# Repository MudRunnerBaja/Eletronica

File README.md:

# Eletronica
Repositório a ser usado apenas pelos membros de eletrônica da equipe baja do Cefet-RJ <br />
Por favor, ao fazer uma alteração no código, indicar o que foi alterado e colocar no READ.ME <br />

## Microcontroladores

- __Pic__:É um microcontrolador de arquitetura Harvard fabricado pela Microchip technology, ele tem a capacidade de processar dados de 8 bits, 16 bits e na versão mais atual, ele é capaz de processar dados de 32 bits. Ele possui uma alta velocidade de processamento devido a sua arquitetura Harvard, além disso, as famílias do MCU Pic  tem núcleos de processamento de 12bits, 14bits e 16bits, e trabalham em velocidade 0kHZ 48MHZ e velocidades de 16MIPS em alguns modelos.<br />   

- __Arduino__:Arduino é uma plataforma de prototipagem eletrônica de hardware livre e de placa única, projetada com um microcontrolador Atmel AVR com suporte de entrada/saída embutido, uma linguagem de programação padrão, a qual tem origem em Wiring, e é essencialmente C/C++.  Normalmente é utilizado em projetos mais simples e que não necessitam de conhecimento muito avançado sobre o firmware do microcontrolador (projetos caseiros).<br /> 

- __Esp32__:É um microcontrolador, que emprega um microprocessador de arquitetura Tensilica Xtensa LX6 de 32 bits com variações dual e single core e uma memória SRAM de 512Kb. Possui um clock máximo de 240 MHz. Ele também conta com wifi e bluetooth integrado.<br /> 

- __STM Arm__:STM32 é uma família de microcontroladores de 32 bits produzidos pela STMicroelectronics. Os chips STM32 são agrupados em séries relacionadas que são baseados em torno do mesmo núcleo do processador ARM de 32 bits, como o Cortex-M7, Cortex-M4F, Cortex-M3, Cortex-M0 +, ou Cortex-M0.<br /> 

- __RP2040__: O RP2040 é um microcontrolador de baixo custo e boa performance, criado pela Raspberry Pi. Trata-se de um processador Dual-Core ARM Cortex M0+, rodando em até 133MHz. Possui 264kB de memória SRAM e 2MB de memória Flash integrada na placa e pode ser programado em MicroPhython ou C/C++. O RP2040 possui 26 GPIOs multifunção, com 2x SPI, 2x I2C, 2x UART, 3x ADC de 12-bits e 16 canais PWM. Ela inclui um sensor de temperatura e bibliotecas para tratar ponto flutuante.<br />

### Microcontrolador escolhido pela equipe

O microcontrolador selecionado pela equipe é o RP2040, vendo sua alta performance, baixo custo e a possibilidade de ser programado pela IDE do arduino. A possibilidade de ser programado pela IDE do Arduino cria uma facilidade pela alta quantidade de bibliotecas, documentações e a familiaridade com a linguaguem de programação. Para usar esse microcontrolador, usamos a placa micro-controlada Raspberry Pi Pico.<br />

__Raspberry Pi Pico__

## Projetos
No momento foram implementadas as seguintes funcionalidades no carro:<br />

<ul>
  <li>Medição da temperatura da CVT</li>
  <li>GPS para localização e mapeamento do carro</li>
  <li>Medidor de combustível</li>
  <li>Leitura do RPM e da Velocidade</li>
  <li>Telemetria do carro</li>
  <li>Armazenamento de dados</li>
  <li>Chamada para o box</li>
</ul><br />

### Medição da temperatura da CVT
Atualmente, muitas equipes sofrem com superaquecimento gerado não só pelo atrito dos componentes presentes na CVT, como também pela falta de ventilação do local. Para resolver essa situação, a equipe decidiu desenvolver um sistema capaz de coletar a temperatura relativa à caixa interna da proteção da CVT, e enviar esses dados pela telemetria para o box. Dessa forma, podemos evitar o rompimento da correia ao detectar um sinal de aquecimento dentro do local. <br />

Após uma análise dos módulos a serem utilizados, o escolhido foi o módulo max6675 junto ao termopar tipo K, pois: <br />

<ul>
  <li>Atende a faixa de temperatura esperada (300 ºC)</li>
  <li>Possui o cabo revestido para não afetar no dado </li>
  <li>Possui uma boa precisão </li>
  <li>Facilidade de implementação no código </li>
  <li>Comunicação rápida (SPI) </li>
  <li>Ótimo custo benefício </li>
  <li>Possui na biblioteca do PROTEUS </li>
</ul><br />

<br />
*Fig 3 - Termopar max6675*<br />

```c
 /*
Código do pic 18f4550 para simulação da temperatura da CVT

Habilitar as seguintes bibliotecas:
- Lcd  e Lcd_Constants
- SPI
- Conversions e C_String e C_Type
- Uart
- C_Stdlib

Clock padrão: 20MHz
*/

#include <built_in.h>
#define tempmax 120

sbit LCD_RS at RB5_bit;
sbit LCD_EN at RB4_bit;
sbit LCD_D4 at RB3_bit;
sbit LCD_D5 at RB2_bit;
sbit LCD_D6 at RB1_bit;
sbit LCD_D7 at RB0_bit;

sbit LCD_RS_Direction at TRISB5_bit;
sbit LCD_EN_Direction at TRISB4_bit;
sbit LCD_D4_Direction at TRISB3_bit;
sbit LCD_D5_Direction at TRISB2_bit;
sbit LCD_D6_Direction at TRISB1_bit;
sbit LCD_D7_Direction at TRISB0_bit;

sbit MAX6675_CS at RC0_Bit;
sbit MAX6675_CS_Direction at TRISC0_Bit;

union{
  char state:1;
  char deviceID:1;
  char open:1;
  char temperature:12;
  char sign:1;
  unsigned output;
}Max6675Data;

void MAX6675_Init(){
  MAX6675_CS_Direction = 0;
  MAX6675_CS = 1;
}

unsigned Max6675_Read(){
unsigned tmp;
  MAX6675_CS = 0;
  Hi(tmp) = SPI1_Read(0);
  Lo(tmp) = SPI1_Read(0);
  MAX6675_CS = 1;
  return(tmp);
}

void main(){
char texto[8];
int temperatura;
   PCFG3_bit = 1; PCFG2_bit = 1; PCFG1_bit = 1; PCFG0_bit = 1;
   UART1_Init(9600);
   SPI1_Init();
   MAX6675_Init();
   Lcd_Init();
   Lcd_Cmd( _LCD_CURSOR_OFF );
   Lcd_Cmd( _LCD_CLEAR );
   Lcd_Out( 1, 6, "Temperatura CVT" );
   TRISD = 0;

   while(1)
   {
      *(unsigned*)&Max6675Data = MAX6675_Read();

      WordToStr( Max6675Data.temperature >> 1, texto );
      Lcd_Out( 2, 1, "Temp: " );
      Lcd_Out_CP( texto+2 );
      Lcd_Chr_CP( 223 );
      Lcd_Chr_CP( 'C' );
      UART1_Write_Text("temperatura:");
      UART1_Write_Text(texto);
      UART1_Write(13);

      temperatura = atoi(texto);

      if (temperatura >= tempmax){
      LATD.F0 = 1;
      }
      else{
      LATD.F0 = 0;
      }
      Delay_ms( 1000 );
   }
}
```

### GPS para localização e mapeamento do carro
O mapeamento de percurso é uma informação de suma importância para nossa equipe, visto que, com ela, é possível analisarmos possíveis falhas de direção, analisar as maiores dificuldades de nossos pilotos, saber se e onde o carro parou, e entre outros dados. O módulo GPS serve para transmitir em tempo real a localização do baja, a partir de dados como a longitude e a latitude. Esses dados podem posteriormente serem processados para mapear os locais visitados pelo carro, bem como sua atual posição. <br />

O módulo escolhido pela equipe foi o  GPS GY-NEO6MV2, por ser mais barato e de fácil utilização: <br />

<br />
*Fig 4 - GPS GY-NEO6MV2*<br />

```c
/*
Código do pic 18f4550 para simulação do GPS

Habilitar as seguintes bibliotecas:
- UART
- C_String

Clock padrão: 20MHz
*/

char txt[768];   // variavel txt para guardar todos os caracteres enviados pelo GPS
char *string;    // ponteiro para guardar a informação de interesse
int i,count,value;

void GPS(){
      int j;
      string = strstr(txt,"$GPGGA");    //String GPGGA contem as informações de latitude e longitude

      // Se a variavel string não for vazia, enviamos a latitude e longitude pela telemetria
      if(string != 0) {
          UART_Write_Text("latitude:");
          for(j = 18; j<27; j++)
              UART_Write(string[j]);
          UART_Write(13);
          UART_Write_Text("longitude:");
          for(j = 30; j<40; j++)
              UART_Write(string[j]);
          UART_Write(13);
      }
}

void interrupt(){
     if(TMR1IF_bit){
              count++;
              TMR1H= 0x0B;
              TMR1L= 0xDC;
              TMR1IF_bit = 0;
     }

     if(RCIF_bit){
              txt[i++] = UART1_Read();
              if(i==768) i=0;
              RCIF_bit = 0;
     }
}

void main() {
           PCFG3_bit = 1; PCFG2_bit = 1; PCFG1_bit = 1; PCFG0_bit = 1; // setando PORTA como digital ( evitar bugs )
           UART1_Init(9600);

           /*Configuração do timer 1 para obter o estouro desejado em ms
             Valores obtidos utilizando o clock padrão de 20MHz e preescaler de 8

              TMR1H = 0x0B;  TMR1L = 0xDC; ----> estouro de 100ms
              TMR1H = 0x85;  TMR1L = 0xEE; ----> estouro de 50ms
              TMR1H = 0xE7;  TMR1L = 0x96; ----> estouro de 10ms
              TMR1H = 0xF3;  TMR1L = 0xCB; ----> estouro de 5ms
              TMR1H = 0xFD;  TMR1L = 0x8F; ----> estouro de 1ms

           */
           TMR1IE_bit = 1;
           T1CON = 0b10110001;
           TMR1H = 0x0B;  TMR1L = 0xDC;

           TRISC.F0 = 0; // porta rc0 definida como saída

           // habilitando as interrupções globais, por periféricos e por UART
           GIE_bit = 1;
           PEIE_bit = 1;
           RCIE_bit = 1;

           while(1){

                    // count é incrementado a cada 100ms pelo timer 1, logo esse if será executado a cada 1segundo
                     if (count == 10){
                          count = 0;
                          value = ~value;
                          LATC.F0 = value;
                          GPS();
                     }

           }
}
```
### Medidor de combustível
O sistema de controle de nível de combustível é um dos circuitos mais importantes no carro, visto que com a noção do volume de gasolina presente no tanque, é possível prevenir a pane seca, que elimina a equipe da prova. Portanto, visando obter um maior tempo de carro na pista sem precisar reabastecer, é imprescindível que tenhamos um bom funcionamento nesse sistema.<br /> 

O módulo escolhido pela equipe foi o  LJC18A3,pois possui uma boa sensibilidade e é ajustável, permitindo uma melhor calibração. Já possuímos esses sensores na oficina e tivemos bons resultados com ele.<br />

<br />
*Fig 5 - Sensor capacitivo LJC18A3*<br />
### Leitura do RPM e da Velocidade

#### Velocidade
A velocidade do carro é um dado muito importante de se adquirir, visto que dá dados ao piloto para testar as melhores condições para fazer uma curva ou passar um obstáculo e é utilizada em diversos testes para a equipe. Com isso em mente, foi implementado um sensor de efeito hall, o qual detectava a pessagem de imãs no disco de freio. Posteriormente, vendo a imprecisão na aquisição da velocidade, causada pela folga axial no eixo da roda, o sistema de aquisição de velocidade foi substituido pela aquisição via GPS, a qual tem uma precisão de 0.1m/s.<br />

#### RPM
O motor de um baja é seu coração, portanto, controlar seu ‘batimento’ (RPM) é de suma importância para o time como um todo. É um dado imprescindível para análise de comportamento do motor, setagem de motor para TF, esforço do motor, quando mostrado ao piloto e entre outras situações.<br />

O motor utilizado possui 4 tempos que são: a admissão, a compressão, a explosão e a exaustão. Ao efetuar um ciclo completo (admissão, compressão, explosão e exaustão), uma indução eletromagnética da corrente é gerada pela bobina da vela. Para conseguir um bom valor de RPM, o sinal do motor precisa ser tratado antes dele ser transmitido para a placa. Esse tratamento de sinal se faz por filtros elétricos; com esse procedimento se espera ter um sinal na forma de onda quadrática com amplitude máxima de 3.3V.<br />

<br />
*Fig 7 - Sinal da bobina primária do motor sem o filtro e com o filtro*<br /> 

<br />
*Fig 8 - Filtro atual implementado pela equipe*<br />

### Telemetria
Dado agora que já somos capazes de implementar na prática todos os projetos acima mencionados, damos início ao nosso projeto da Telemetria. Irá funcionar como um sistema supervisório, em que todos os dados coletados são enviados por meio de um transmissor para nosso box. Dessa forma, todos da equipe poderam observar e perceber o que está se passando no carro, ajudando nas tomadas de decisão durante a prova.<br />
De modo geral, serão 2 desafios a serem superados. O primeiro consiste em juntar todos os projetos em um só. Já o segundo se resume na criação de um sistema supervisório e interativo, o qual ficou decidido que será um site.<br />
Para transmitir nossos dados, a equipe optou por escolher os seguintes componentes:<br />

- __Módulo HC-12:__ Tal módulo foi selecionado pela sua facilidade de uso, possui um custo baixo e atender a meta de telemetria de 800m, se utilizada com uma antena adequada. A antena helicoidal (que vem junto ao módulo) tem uma limitação de até 300-500m dependendo do local. É importante estar atento a escolha do próprio módulo, devendo ele ser ORIGINAL. Existem versões genéricas que limitam o alcance.<br />  

- __Antena monopólo vertical:__ https://www.youtube.com/watch?v=nQ4qYwILRjA Nesse video, há uma validação pratica com 2 diferentes antenas usando o HC12. Explicando o porquê de utilizar a antena monopólio vertical. Como ela pode ser fabricada por nós mesmos, de forma simples e barata, ela foi selecionada.<br />

<br />
*Fig 10 - Módulo HC 12 e antena*<br />

### Chamada para o box
A comunicação entre o piloto e o box durante a competição é algo muito importante para a equipe. Dessa forma, decidimos implementar um sistema de chamada para o box que será adicionado ao projeto da telemetria que a equipe já tem. Esse sistema consiste em uma comunicação bilateral onde o piloto tem a capacidade de avisar a equipe que ele está indo para o box ou a equipe pode chamar o piloto para ir para o box para reabastecer ou devido a um problema detectado no carro. <br />
A implementação será feita por meio da adição de um diodo LED no painel do carro para avisar o piloto que ele precisa ir para o box (a equipe chamando o piloto) e uma chave Push Button (Botão) para o piloto avisar a equipe que está indo ou querendo ir para o box. <br />

<br />
*Fig 11 - LEDs e Push Button*br />

## Testes
Os seguintes testes estão em desenvolvimento para auxíliar a equipe quanto a otimização dos componentes do carro<:br />

<ul>
  <li>Teste de Strain Gauge</li>
  <li>Teste de retomada e aceleração</li>
  <li>Teste de CVT Tunning</li>
  <li>Teste da variação do coeficiente de atrito da pastilha e do disco</li>
  <li>Teste de vibração</li>
</ul><br />

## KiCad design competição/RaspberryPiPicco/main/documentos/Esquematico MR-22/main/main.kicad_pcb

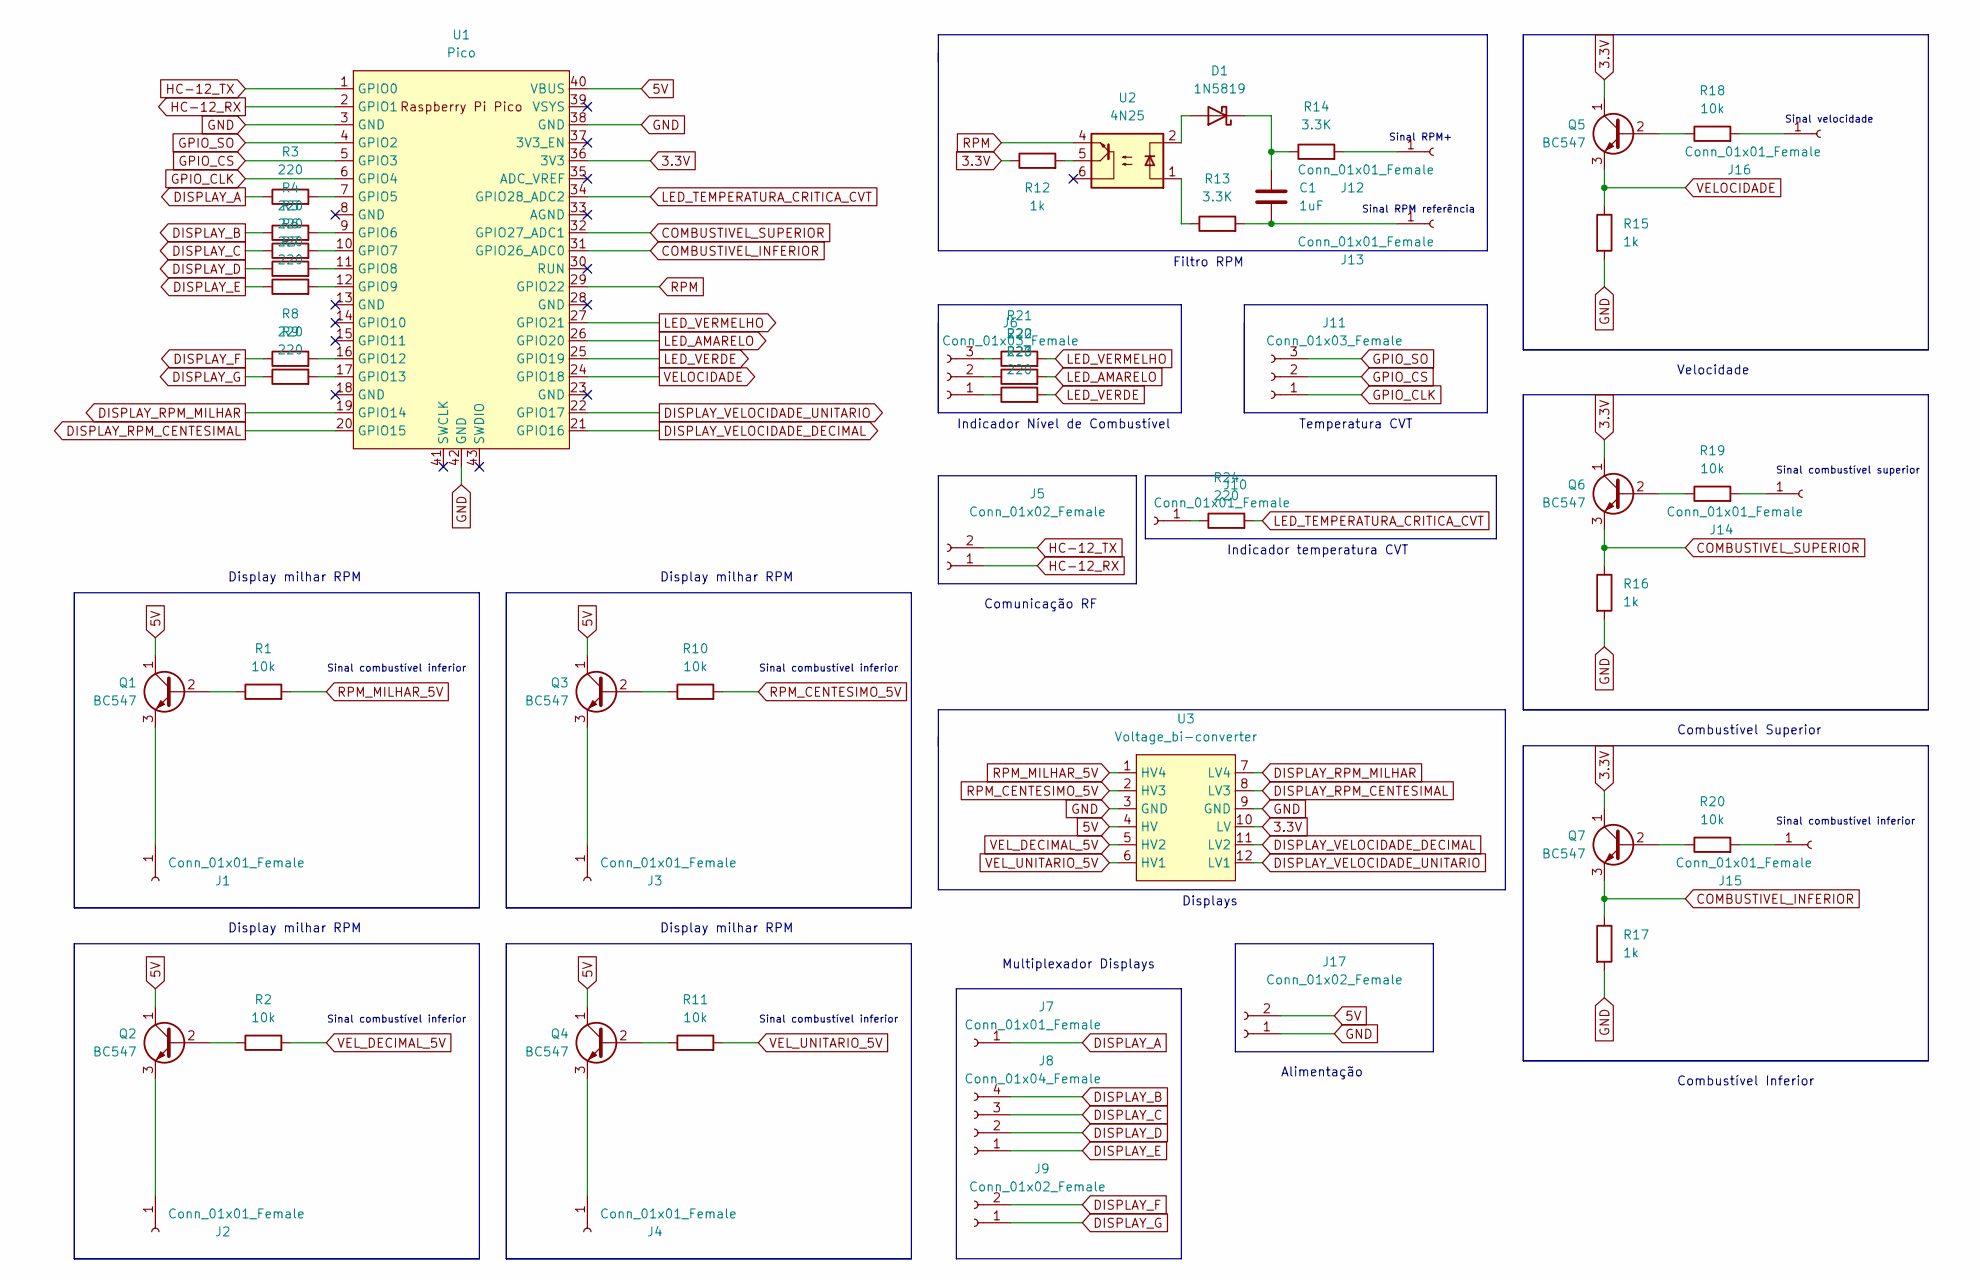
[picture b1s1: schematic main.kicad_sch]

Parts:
C1: 1uF; CP_Radial_D5.0mm_P2.00mm
D1: 1N5819; D_DO-41_SOD81_P10.16mm_Horizontal
J1, J2, J3, J4, J7, J10, J12, J13, J14, J15, J16: Conn_01x01_Female; PinSocket_1x01_P2.00mm_Vertical
J5, J9, J17: Conn_01x02_Female; PinSocket_1x02_P2.00mm_Vertical
J6, J11: Conn_01x03_Female; PinSocket_1x03_P2.00mm_Vertical
J8: Conn_01x04_Female; PinSocket_1x04_P2.00mm_Vertical
Q1, Q2, Q3, Q4, Q5, Q6, Q7: BC547; TO-92_Inline
R1, R2, R10, R11, R18, R19, R20: 10k; R_Axial_DIN0204_L3.6mm_D1.6mm_P5.08mm_Horizontal
R3, R4, R5, R6, R7, R8, R9, R21, R22, R23, R24: 220; R_Axial_DIN0204_L3.6mm_D1.6mm_P5.08mm_Horizontal
R12, R15, R16, R17: 1k; R_Axial_DIN0204_L3.6mm_D1.6mm_P5.08mm_Horizontal
R13, R14: 3.3K; R_Axial_DIN0204_L3.6mm_D1.6mm_P5.08mm_Horizontal
U1: Pico; RPi_Pico_SMD_TH
U2: 4N25; DIP-6_W7.62mm
U3: Voltage_bi-converter; bi_voltage-converter

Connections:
3.3V: Q5.1 (C), Q6.1 (C), Q7.1 (C), R12.1, U1.36 (3V3), U3.10 (LV)
5V: J17.2, Q1.1 (C), Q2.1 (C), Q3.1 (C), Q4.1 (C), U1.40 (VBUS), U3.4 (HV)
COMBUSTIVEL_INFERIOR: Q7.3 (E), R17.1, U1.31 (GPIO26_ADC0)
COMBUSTIVEL_SUPERIOR: Q6.3 (E), R16.1, U1.32 (GPIO27_ADC1)
DISPLAY_A: J7.1, R3.1
DISPLAY_B: J8.4, R4.1
DISPLAY_C: J8.3, R5.1
DISPLAY_D: J8.2, R6.1
DISPLAY_E: J8.1, R7.1
DISPLAY_F: J9.2, R8.1
DISPLAY_G: J9.1, R9.1
DISPLAY_RPM_CENTESIMAL: U1.20 (GPIO15), U3.8 (LV3)
DISPLAY_RPM_MILHAR: U1.19 (GPIO14), U3.7 (LV4)
DISPLAY_VELOCIDADE_DECIMAL: U1.21 (GPIO16), U3.11 (LV2)
DISPLAY_VELOCIDADE_UNITARIO: U1.22 (GPIO17), U3.12 (LV1)
GND: J17.1, R15.2, R16.2, R17.2, U1.3 (GND), U1.38 (GND), U1.42 (GND), U3.3 (GND), U3.9 (GND)
GPIO_CLK: J11.1, U1.6 (GPIO4)
GPIO_CS: J11.2, U1.5 (GPIO3)
GPIO_SO: J11.3, U1.4 (GPIO2)
HC-12_RX: J5.1, U1.2 (GPIO1)
HC-12_TX: J5.2, U1.1 (GPIO0)
LED_AMARELO: R22.2, U1.26 (GPIO20)
LED_TEMPERATURA_CRITICA_CVT: R24.2, U1.34 (GPIO28_ADC2)
LED_VERDE: R23.2, U1.25 (GPIO19)
LED_VERMELHO: R21.2, U1.27 (GPIO21)
unnamed: C1.1, D1.1 (K), R14.1
unnamed: C1.2, J13.1, R13.2
unnamed: D1.2 (A), U2.2
unnamed: J1.1, Q1.3 (E)
unnamed: J2.1, Q2.3 (E)
unnamed: J3.1, Q3.3 (E)
unnamed: J4.1, Q4.3 (E)
unnamed: J6.1, R23.1
unnamed: J6.2, R22.1
unnamed: J6.3, R21.1
unnamed: J10.1, R24.1
unnamed: J12.1, R14.2
unnamed: J14.1, R19.2
unnamed: J15.1, R20.2
unnamed: J16.1, R18.2
unnamed: Q1.2 (B), R1.1
unnamed: Q2.2 (B), R2.1
unnamed: Q3.2 (B), R10.1
unnamed: Q4.2 (B), R11.1
unnamed: Q5.2 (B), R18.1
unnamed: Q6.2 (B), R19.1
unnamed: Q7.2 (B), R20.1
unnamed: R3.2, U1.7 (GPIO5)
unnamed: R4.2, U1.9 (GPIO6)
unnamed: R5.2, U1.10 (GPIO7)
unnamed: R6.2, U1.11 (GPIO8)
unnamed: R7.2, U1.12 (GPIO9)
unnamed: R8.2, U1.16 (GPIO12)
unnamed: R9.2, U1.17 (GPIO13)
unnamed: R12.2, U2.5
unnamed: R13.1, U2.1
RPM: U1.29 (GPIO22), U2.4
RPM_CENTESIMO_5V: R10.2, U3.2 (HV3)
RPM_MILHAR_5V: R1.2, U3.1 (HV4)
VELOCIDADE: Q5.3 (E), R15.1, U1.24 (GPIO18)
VEL_DECIMAL_5V: R2.2, U3.5 (HV2)
VEL_UNITARIO_5V: R11.2, U3.6 (HV1)

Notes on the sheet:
Sinal combustível inferior
Sinal velocidade
Display milhar RPM
Displays
Alimentação
Temperatura CVT
Indicador temperatura CVT
Velocidade
Combustível Inferior
Indicador Nível de Combustível
Sinal combustível superior
Comunicação RF
Sinal RPM+
Sinal RPM referência
Filtro RPM
Multiplexador Displays
Combustível Superior

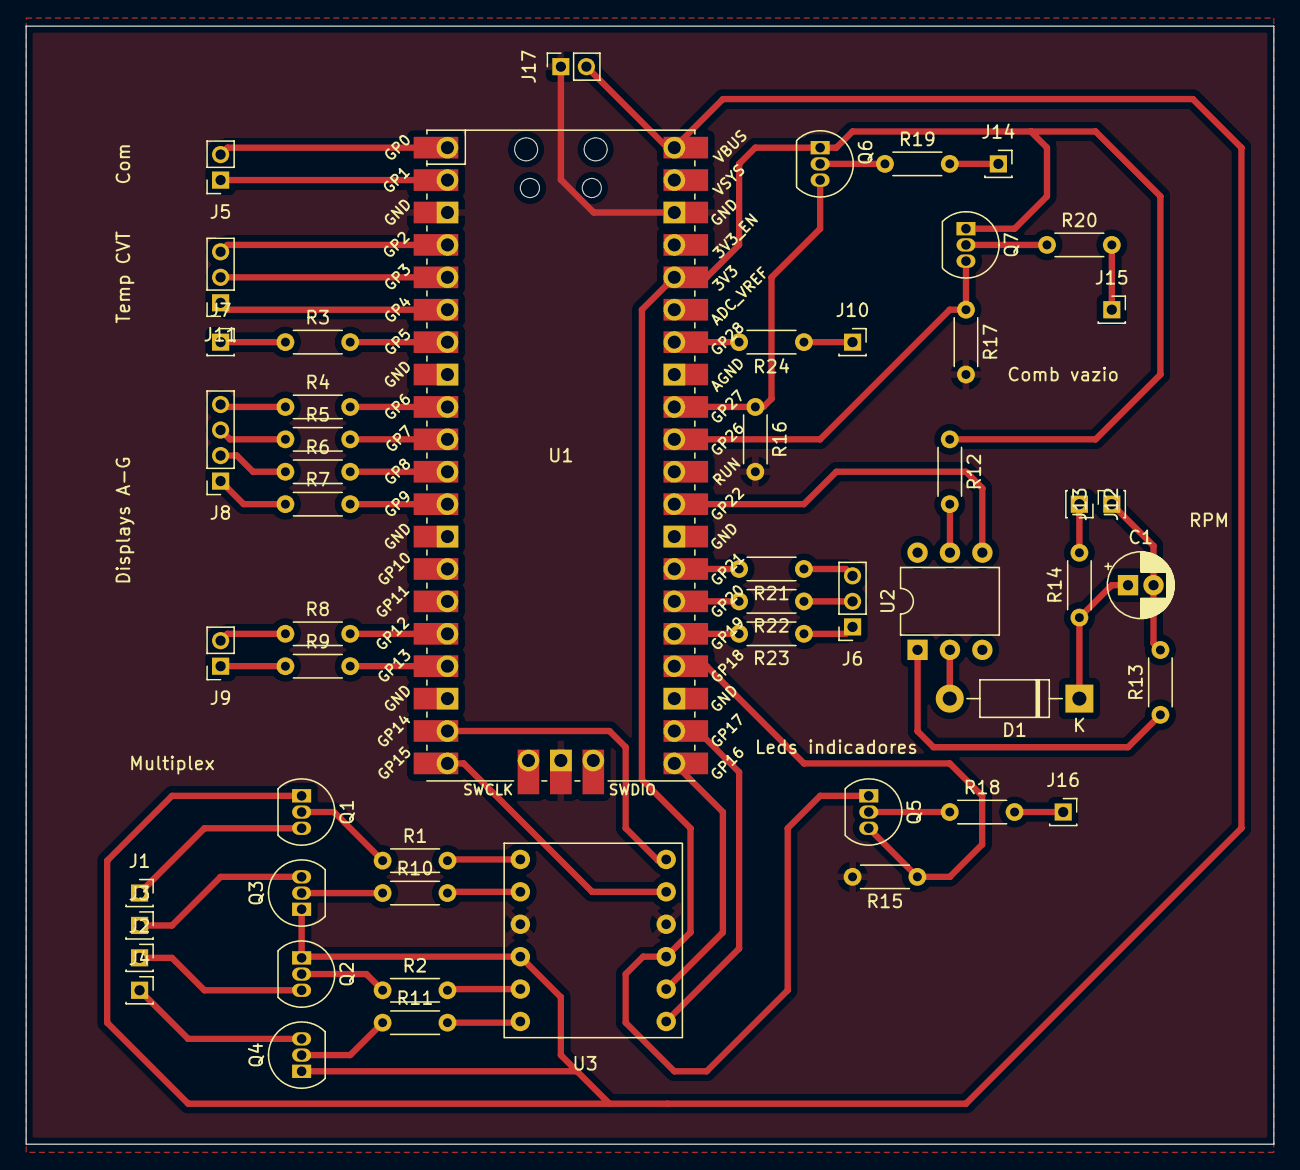
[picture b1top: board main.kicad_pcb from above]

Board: 2 copper layers, 97.8 x 87.6 mm, 53 parts (0 on the bottom side), 62 nets.

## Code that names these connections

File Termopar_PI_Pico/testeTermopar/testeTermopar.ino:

// Teste Termopar tipo k

#include <max6675.h>
  
/* Definições: GPIOs do Arduino utilizado na comunicação com o 
   MAX6675 */
#define GPIO_SO       2
#define GPIO_CS       3  
#define GPIO_CLK      4
 
/* Definição: baudrate da comunicação com Serial Monitor */
#define BAUDRATE_SERIAL_MONITOR    115200
 
/* Definição: tempo entre leituras do MAX6675 */
#define TEMPO_ENTRE_LEITURAS             1000 //ms
 
/* Criação de objeto para comunicação com termopar */
MAX6675 termopar(GPIO_CLK, GPIO_CS, GPIO_SO);
  
void setup()
{
    Serial.begin(BAUDRATE_SERIAL_MONITOR);
}
 
/* Programa principal */
void loop() 
{  
    Serial.print("Temperatura: "); 
    Serial.print(termopar.readCelsius());
    Serial.println("C"); 
    delay(TEMPO_ENTRE_LEITURAS);
}

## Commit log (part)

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2020-05-20 simulacao
2020-05-21 organizando o git
2020-05-21 Projeto telemetria antigo
2020-05-31 correcao bugs
2020-07-23 Create main.c
    Código principal atualizado com strain gauge *nao testado*
2020-12-07 Troquei o nome do .jpg
2020-12-26 adicionando imagem da simulação do box
2021-04-03 Create placasEagle
2021-07-12 Adicionado o arquivo de 30m
2021-08-17 Bump ini from 1.3.5 to 1.3.8 in /telemetria/telemetria_v2
    Bumps [ini](https://github.com/isaacs/ini) from 1.3.5 to 1.3.8.
    - [Release notes](https://github.com/isaacs/ini/releases)
    - [Commits](https://github.com/isaacs/ini/compare/v1.3.5...v1.3.8)
    ---
    updated-dependencies:
    - dependency-name: ini
2021-08-23 Iniciando telemetria e re-organização das pastas
2022-02-17 Adicionado sistema com o tema da equipe
2022-02-20 Adicionado rota usuário
2022-02-21 Adicionado GPS
2022-04-07 Atualização de pinos + alterações servidor
2022-04-12 Correção rpm
2022-04-15 Esquema da placa do display
2022-07-27 Atualização da Placa Principal
    Corrigido um pequeno erro nas trilhas e adicionada uma pequena modificação no design
2022-08-17 Adicionado a função de velocidade
2022-08-22 Novas funções e corrigido erros de gravação
2022-08-23 Falhas corrigidas
2022-08-31 Portas corrigidas para o novo modelo de placa
2022-09-20 IC Charlieplexado
    Tentativa de manter o brilho do display reduzindo o consumo de corrente. Se bem sucedido:
    - Mantém o projeto da placa
    - Mantém o custo dos componentes da placa
    - Evita o uso de gambiarras e soluções externas (como placas com transistores)
2022-09-21 Bump minimist from 1.2.5 to 1.2.6 in /telemetria/Antigo
    Bumps [minimist](https://github.com/substack/minimist) from 1.2.5 to 1.2.6.
    - [Release notes](https://github.com/substack/minimist/releases)
    - [Commits](https://github.com/substack/minimist/compare/1.2.5...1.2.6)
    ---
    updated-dependencies:
    - dependency-name: minimist
2022-09-21 Bump moment-timezone in /telemetria/Sistema_tema_equipe/Sistema
    Bumps [moment-timezone](https://github.com/moment/moment-timezone) from 0.5.34 to 0.5.37.
    - [Release notes](https://github.com/moment/moment-timezone/releases)
    - [Changelog](https://github.com/moment/moment-timezone/blob/develop/changelog.md)
    - [Commits](https://github.com/moment/moment-timezone/compare/0.5.34...0.5.37)
    ---
    updated-dependencies:
2022-09-21 Bump sqlite3 in /telemetria/Sistema_tema_equipe/Sistema
    Bumps [sqlite3](https://github.com/TryGhost/node-sqlite3) from 5.0.2 to 5.0.3.
    - [Release notes](https://github.com/TryGhost/node-sqlite3/releases)
    - [Changelog](https://github.com/TryGhost/node-sqlite3/blob/master/CHANGELOG.md)
    - [Commits](https://github.com/TryGhost/node-sqlite3/compare/v5.0.2...v5.0.3)
    ---
    updated-dependencies:
2022-09-30 Implementado múltipla criação de arquivos no SD
2022-10-20 Update SDCard
2022-10-25 Revert "Update sdcard.c"
    This reverts commit ab002c03ba32cec3cbdfa6e41cc4ba4b598456bb.
2022-11-04 Esquemática do novo filtro de RPM
2022-11-15 Testes pré-regional
2022-12-08 Bump qs and express in /telemetria/Antigo
    Bumps [qs](https://github.com/ljharb/qs) to 6.11.0 and updates ancestor dependency [express](https://github.com/expressjs/express). These dependencies need to be updated together.
    Updates `qs` from 6.7.0 to 6.11.0
    - [Release notes](https://github.com/ljharb/qs/releases)
    - [Changelog](https://github.com/ljharb/qs/blob/main/CHANGELOG.md)
    - [Commits](https://github.com/ljharb/qs/compare/v6.7.0...v6.11.0)
    Updates `express` from 4.17.1 to 4.18.2
2022-12-20 implementando novo gps
2022-12-22 Preparação do setup
2022-12-22 Setup timer e getcomb
2022-12-22 fault handling sdcard
2022-12-22 debugging code
2022-12-25 Corrigido erro na atribuição de uma função
2023-01-19 Código-Teste para Otimização
    Limitando tempo de encoding do GPS para evitar prender o processador por longos períodos de tempo;
    Checagem se os dados salvos foram recentemente atualizados ou não;
    É necessário reestruturar o sistema de biblioteca
2023-01-29 Implementado a interface de configuração
    Ainda a fazer:
    Salvar horário usando o gps
    Não gravar dados enquanto o gps não estiver sincronizado com os satelites
2023-02-02 Teste Completo
2023-02-06 fixes
2023-02-07 Comentarios adicionados
2023-02-10 Pre-Teste
2023-02-12 Contador de rpm da movida
2023-02-13 Adaptaçao cartao SD CVT Tuning
2023-02-16 Fix i2c
2023-02-17 Renaming and changing to header files
2023-02-21 Improved interface
2023-02-23 Bump sequelize in /telemetria/Sistema_tema_equipe/Sistema
    Bumps [sequelize](https://github.com/sequelize/sequelize) from 6.16.1 to 6.28.2.
    - [Release notes](https://github.com/sequelize/sequelize/releases)
    - [Commits](https://github.com/sequelize/sequelize/compare/v6.16.1...v6.28.2)
    ---
    updated-dependencies:
    - dependency-name: sequelize
2023-02-24 Added new functions
2023-02-25 Bump sequelize in /telemetria/Sistema_tema_equipe/Sistema
    Bumps [sequelize](https://github.com/sequelize/sequelize) from 6.16.1 to 6.29.0.
    - [Release notes](https://github.com/sequelize/sequelize/releases)
    - [Commits](https://github.com/sequelize/sequelize/compare/v6.16.1...v6.29.0)
    ---
    updated-dependencies:
    - dependency-name: sequelize
2023-03-07 Bump minimist in /telemetria/Sistema_tema_equipe/Sistema
    Bumps [minimist](https://github.com/minimistjs/minimist) from 1.2.5 to 1.2.8.
    - [Release notes](https://github.com/minimistjs/minimist/releases)
    - [Changelog](https://github.com/minimistjs/minimist/blob/main/CHANGELOG.md)
    - [Commits](https://github.com/minimistjs/minimist/compare/v1.2.5...v1.2.8)
    ---
    updated-dependencies:
2023-04-05 Add files via upload
    Teste simples! Só para ver quando o receptor parou de receber!
2023-05-31 Atualizando Testes de Telemetria
    Agora envia uma data que é quebrada em dias/mes/ano de um sender para um receiver.
    a distância do sinal chegou a 130m sem obstruções tranquilamente.
2023-07-06 Teste de Distancia Standalone adicionado
2023-07-06 Teste comunicacao serial1 e serial2 pico consigo mesmo (Sem sucesso)
2023-08-01 Atualizado pra main. Precisa de revisao
2023-08-16 Implementação no codigo da placa principal
2023-12-11 readme e configurações de projeto
2023-12-16 Teste telemetria pico-ft232 adaptado
2024-01-10 back end funcionando usando serial por emulado
    informações no arquivo teste emulacao serial, mongo db.informacoes só recebe o id do data sheet e não os valores verificar parser
2024-01-11 inicio projeto frontend
2024-01-24 json stringfy arduino data back -> front
2024-02-06 Update TestePressaoFreio.ino
    Adicionado comentarios
2024-02-20 Adicao de libs ao novo sketch placa central
2024-02-21 Bump ip from 2.0.0 to 2.0.1 in /telemetria/frontend
    Bumps [ip](https://github.com/indutny/node-ip) from 2.0.0 to 2.0.1.
    - [Commits](https://github.com/indutny/node-ip/compare/v2.0.0...v2.0.1)
    ---
    updated-dependencies:
    - dependency-name: ip
    dependency-type: indirect
2024-02-29 Libs sensor temperatura mlx90614
2024-03-06 Codigos de teste CAN-BUS funcional
2024-03-18 cod placa central WIP
2024-03-23 Estruturacao das bibliotecas compilavel para arduino-pico
2024-03-29 Bump express from 4.18.2 to 4.19.2 in /telemetria/frontend
    Bumps [express](https://github.com/expressjs/express) from 4.18.2 to 4.19.2.
    - [Release notes](https://github.com/expressjs/express/releases)
    - [Changelog](https://github.com/expressjs/express/blob/master/History.md)
    - [Commits](https://github.com/expressjs/express/compare/4.18.2...4.19.2)
    ---
    updated-dependencies:
2024-05-09 implementacao combustivel
2024-05-14 Teste do limite de rpm
2024-05-20 Correções e ajuste biblioteca GPS
2024-05-24 WIP refatoracao telemetria - separacao da logica e configuracao de infra
2024-06-04 Transformando classes em singletons
2024-06-11 Implementado menus e layout atualizado
2024-06-14 static struct com dados
2024-07-22 correcoes inicializacao
2024-08-03 struct global de dados para simplificar troca de info
2025-02-20 fix antigos
2025-02-27 substituicao prints debug
2025-04-29 Bump http-proxy-middleware and @angular-devkit/build-angular
    Bumps [http-proxy-middleware](https://github.com/chimurai/http-proxy-middleware) to 3.0.5 and updates ancestor dependency [@angular-devkit/build-angular](https://github.com/angular/angular-cli). Thes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
    Updates `http-proxy-middleware` from 2.0.6 to 3.0.5
    - [Release notes](https://github.com/chimurai/http-proxy-middleware/releases)
    - [Changelog](https://github.com/chimurai/http-proxy-middleware/blob/master/CHANGELOG.md)
    - [Commits](https://github.com/chimurai/http-proxy-middleware/compare/v2.0.6...v3.0.5)
    Updates `@angular-devkit/build-angular` from 17.1.1 to 19.2.9
2025-05-29 can bus compilando, velocidade e rpm funcionais
2025-06-04 Bump webpack-dev-server and @angular-devkit/build-angular
    Bumps [webpack-dev-server](https://github.com/webpack/webpack-dev-server) to 5.2.1 and updates ancestor dependency [@angular-devkit/build-angular](https://github.com/angular/angular-cli). These depen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
    Updates `webpack-dev-server` from 4.15.1 to 5.2.1
    - [Release notes](https://github.com/webpack/webpack-dev-server/releases)
    - [Changelog](https://github.com/webpack/webpack-dev-server/blob/master/CHANGELOG.md)
    - [Commits](https://github.com/webpack/webpack-dev-server/compare/v4.15.1...v5.2.1)
    Updates `@angular-devkit/build-angular` from 17.1.1 to 20.0.1
2025-06-09 Codigo modificado para o primeiro teste
2025-06-10 codificacao funcional, TODO: decodificacao e reorganizacao de pacotes
2025-08-19 codigo que ta no pc de eletronica
2025-09-09 é necessário fazer structs menores para passar os dados
2025-09-10 codigo enviando dados com sucesso pela telemetria. Ainda é necessário fazer um cleanup no código para a versão final
2025-09-19 mudei alguma coisas de dados
2025-09-25 verifiquei k
2025-10-28 Bump validator in /telemetria/old/Sistema_tema_equipe/Sistema
    Bumps [validator](https://github.com/validatorjs/validator.js) from 13.7.0 to 13.15.20.
    - [Release notes](https://github.com/validatorjs/validator.js/releases)
    - [Changelog](https://github.com/validatorjs/validator.js/blob/master/CHANGELOG.md)
    - [Commits](https://github.com/validatorjs/validator.js/compare/13.7.0...13.15.20)
    ---
    updated-dependencies:
2025-11-26 Bump node-forge from 1.3.1 to 1.3.2 in /telemetria/frontend
    Bumps [node-forge](https://github.com/digitalbazaar/forge) from 1.3.1 to 1.3.2.
    - [Changelog](https://github.com/digitalbazaar/forge/blob/main/CHANGELOG.md)
    - [Commits](https://github.com/digitalbazaar/forge/compare/v1.3.1...v1.3.2)
    ---
    updated-dependencies:
    - dependency-name: node-forge
2025-12-01 Bump express from 4.18.2 to 4.22.0 in /telemetria/backend
    Bumps [express](https://github.com/expressjs/express) from 4.18.2 to 4.22.0.
    - [Release notes](https://github.com/expressjs/express/releases)
    - [Changelog](https://github.com/expressjs/express/blob/4.22.0/History.md)
    - [Commits](https://github.com/expressjs/express/compare/4.18.2...4.22.0)
    ---
    updated-dependencies:
2025-12-31 Bump qs and express in /telemetria/old/Antigo
    Bumps [qs](https://github.com/ljharb/qs) to 6.14.1 and updates ancestor dependency [express](https://github.com/expressjs/express). These dependencies need to be updated together.
    Updates `qs` from 6.7.0 to 6.14.1
    - [Changelog](https://github.com/ljharb/qs/blob/main/CHANGELOG.md)
    - [Commits](https://github.com/ljharb/qs/compare/v6.7.0...v6.14.1)
    Updates `express` from 4.17.1 to 4.22.1
    - [Release notes](https://github.com/expressjs/express/releases)
2026-01-21 Bump lodash in /telemetria/old/Sistema_tema_equipe/Sistema
    Bumps [lodash](https://github.com/lodash/lodash) from 4.17.21 to 4.17.23.
    - [Release notes](https://github.com/lodash/lodash/releases)
    - [Commits](https://github.com/lodash/lodash/compare/4.17.21...4.17.23)
    ---
    updated-dependencies:
    - dependency-name: lodash
2026-02-05 Bump semver from 5.7.1 to 5.7.2 in /telemetria/old/Antigo
    Bumps [semver](https://github.com/npm/node-semver) from 5.7.1 to 5.7.2.
    - [Release notes](https://github.com/npm/node-semver/releases)
    - [Changelog](https://github.com/npm/node-semver/blob/v5.7.2/CHANGELOG.md)
    - [Commits](https://github.com/npm/node-semver/compare/v5.7.1...v5.7.2)
    ---
    updated-dependencies:
2026-02-26 sei lá
